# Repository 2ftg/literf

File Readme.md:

## What if hackRF, but cheap?

This repository contains hardware designs and software for the liteRF project,
a low cost, open source Software Defined Radio platform based on the popular HackRF design by Great Scott Gadgets.  

This is a living project and thus not suitable for manufacturing or any use. You have been warned.

We want to reduce the cost and availability problems with the parts chosen for the original HackRF.  
Our target is to at least halve the BOM cost and avoid as many of the unobtainium and obsolete parts.  
Especially those by Maxim.

This whole project started with me finding AT86RF215's on Digikey one night and discovering their IQ interface.   
It was re-invigorated by the [CaribouLite project](https://github.com/cariboulabs/cariboulite/blob/main/docs/smi/README.md) also named Lite and using the AT86RF215.

(photo by fd0 from https://github.com/fd0/hackrf-one-pictures)

This is the original hackRF, want to make it cheaper and to avoid problems with unobtainium parts.

Because all great artists steal, we will consider existing related projects when choosing parts.   
As that gives us access to existing, proven designs with support from the community.

### Component substitutions that have been decided on:
1. Maxim MAX2837+MAX5864 replaced by Microchip AT86RF215. Cheaper, more available.
2. Xilinx XC2C64A-7VQG100C CPLD replaced with Lattice ICE40LP1k-QN84
3. SiLabs/Skyworks Si5351C replaced by Hangzhou Ruimeng Tech MS5351M. Cheaper, AVAILABLE. Might require two or rethinking clocks.

Some links to candidate parts and information on them below.

#### Maxim MAX2837 Transceiver + MAX5864 AFE with AT86RF215
Both of these are expensive and hard to find. It might change now that Analog Devices owns Maxim, or get worse.   
Replacing these is the origin of this project. I had a terrible time sourcing them for my hackRF build.   

MAX2837 info:   
https://www.maximintegrated.com/en/products/comms/wireless-rf/MAX2837.html   
Datasheet: https://datasheets.maximintegrated.com/en/ds/MAX2837.pdf 

MAX5864 info:  
https://www.maximintegrated.com/en/products/analog/data-converters/analog-front-end-ics/MAX5864.html

MAX2837 covers 2300-2700MHz in turn AT86RF215 covers only a part of the same spectrum. The 2400-2400-2483.5MHz ISM band.
This is not a major problem as hacKRF uses a 2.4GHz IF with a SAW filter.   
This is compatible with using AT86RF215.

AT86RF215 info:
https://www.microchip.com/en-us/product/AT86RF215
Datasheet: https://ww1.microchip.com/downloads/en/DeviceDoc/45099A-AT86RF215_E_US_102714_Web.pdf

#### Xilinx XC2C64A-7VQG100C CPLD with Lattice ICE40LP1k-QN84 FPGA
0 stock and 52 week lead time on Digikey, nuff said:   
https://www.digikey.fi/en/products/detail/xilinx-inc/XC2C64A-7VQG100C/949460
Datasheet: https://docs.xilinx.com/v/u/en-US/ds311

In addition to sourcing problems, a 64 macrocell CPLD can't do what we want to the 128Mbit/second 64MHz DDR clocked LVDS interface AT86RF215 has.   
Thus we replace it with Lattice ICE40LP1k-QN84. This has a FOSS toolchain and a free tool chain from the manufacturer.   
It is used in the CaribouLite, so it works with AT86RF215 amd the gateware is under a permissive license. So we are not starting from 100% scratch.  
We need some fast programmable gluelogic here and Lattice iCE40 is a good choise due to low cost, good FOSS community and okay-ish [availability](https://octopart.com/ice40lp1k-qn84-lattice+semiconductor-22303412).   
I might have to reconsider this if I cannot source it or any iCE40 device with the same or larger amount of LUT's. I'm open to suggestions.   
iCE40LP family datasheet:    https://www.latticesemi.com/~/media/LatticeSemi/Documents/DataSheets/iCE/iCE40LPHXFamilyDataSheet.pdf

#### SiLabs/Skyworks Si5351C replaced with Hangzhou Ruimeng Tech MS5351M.

Skyworks Si5351C is in QFN case and has 8 outputs, compared to MS5351M's 3, so some work is likely needed. But they are register compatible and MS5351M 1:1 replaces Si5351B in almost all applications.   
This requires further thought in the clock tree side of things. 

Source and datasheet.   
https://lcsc.com/product-detail/Clock-Generators-Frequency-Synthesizers-PLL_Hangzhou-Ruimeng-Tech-MS5351M_C1509083.html   

QRP-Labs investigation that finds MS5351 meeting or exeeding Si5351.   
http://www.qrp-labs.com/synth/ms5351m.html

Si5351C stock situation:   
https://octopart.com/si5351c-b-gm-silicon+labs-24879781

### Component substitutions that are under consideration:
1. NXP LPC4320FBD144 MCU substitution with something cheaper and more available.
2. TI TPS62410 dual VREG with two Microchip switchers and point of load low noise LDO's for RF. Due to availability and noise.
3. Skyworks SKY13317 RF switch with Maxcend MXD8641. Due to price and availability. Also for better frontend.

Some links to candidate parts and information on them.

NXP LPC4320FBD144 has:   
ARM Cortex-M4F core capable of 204MHz and a Arm Cortex-M0 co-processor running at frequencies up to 204MHz.   
200kB SRAM
High-speed USB 2.0 Host/Device interface.

##### WCH CH32V307VCT6 MCU candidate.
I'm unsure if this is fast enough. It's RISC-V! 
Datasheet+SDK https://github.com/openwch/ch32v307   

LQFP100 case https://lcsc.com/product-detail/Microcontroller-Units-MCUs-MPUs-SOCs_WCH-Jiangsu-Qin-Heng-CH32V307VCT6_C2943979.html

Used in [iCEBreaker 1.99 hardware](https://github.com/icebreaker-fpga/icebreaker/tree/hw-v1.99-evaluation-designs/hardware/v1.99a) with Lattice iCE40UP5K.  

##### NXP i.MXRT MCU candidates

i.MX RT1024 Cortex-M7 @500 MHz 256 kB SRAM 144 LQFP 
i.MX RT1020 Cortex-M7 @500 MHz 256 kB SRAM 100 LQFP & 144 LQFP 

##### TPS62410DRCR info and repalcement candidates

[Octopart shows some stock, but only direct from TI or from Farnell, which is stingy about selling to individuals ](https://octopart.com/search?q=TPS62410DRCR&currency=EUR&specs=0)   
This is annoying and thus needs a good replacement. 

TPS62410 product page with info and datasheet:   
https://www.ti.com/product/TPS62410

##### Maxcend MXD8641 SP4T RF switch
Source and data.
https://lcsc.com/product-detail/RF-Switches_Maxscend-MXD8641_C285559.html

NanoVNA v2, they use Maxcend switches and later also MS5351M.   
https://github.com/nanovna-v2/NanoVNA2

Other Maxcend RF swithces are also available on LCSC.net (https://lcsc.com/products/RF-Switches_980.html?brand=11684)

#### Some parts selection logic I have used:   
Needs to be cheaper than what it's replacing.   
If not cheaper, then more available.   
If possible, already used and thus qualified by somebody else. Possibly lower risk of surprises that way.   
Higher performance than what it is replacing.   
Easier to use use than what it is replacing.      
If possible, the case should be easily soldered and inspected. So more QFN and TQFP, less BGA and LGA.   
Available from JLCPCB SMT assembly, LCSC.com , TME.eu, Mouser or Digikey.

##### Other minor motivations and changes:
PROPER REF DES on PCB.

One of these days I'll clean this up and use the wiki for all the component talk.

#### Contact
[@2ftg1](https://twitter.com/2ftg1/) on Twitter   
As ftg on Ircnet with shell, as ftg on Libera.Chat from time to time.

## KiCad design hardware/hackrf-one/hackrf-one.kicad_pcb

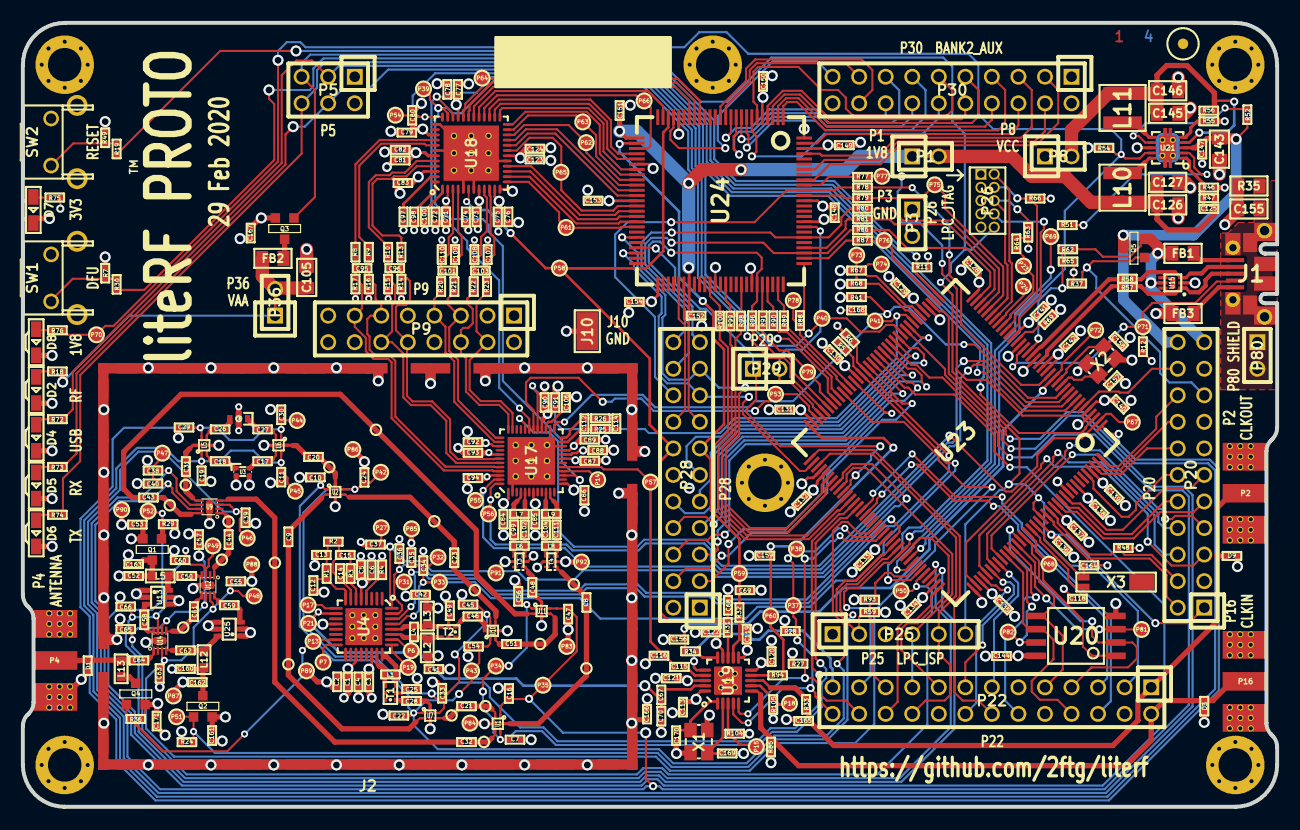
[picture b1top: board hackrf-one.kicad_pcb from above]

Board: 4 copper layers, 120.0 x 75.0 mm, 432 parts (0 on the bottom side), 316 nets.

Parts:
C1, C3, C5, C7, C10, C11, C16, C19, C22, C24, C29, C30, C33, C34, C35, C36, C37, C38, C39, C40, C45, C47, C54, C55, C56, C57, C60, C63, C65, C66, C67, C115, C125: 33pF; GSG-0402
C2, C4, C6, C87, C88, C89, C92, C93, C162, C163: 10nF; GSG-0402
C8, C21, C32, C43, C48, C51, C84, C85, C86, C94, C95, C96, C99, C101, C102, C103, C107, C108, C109, C110: 22pF; GSG-0402
C9, C17, C18, C20, C23, C25, C28, C31, C44, C46, C49, C50, C58, C59, C61, C62, C64, C71, C73, C75, C77, C79, C81, C83, C91, C113, C119, C120, C121, C122, C123, C128, C129, C130, C131, C132, C133, C134, C135, C136, C137, C138, C139, C140, C141, C142, C144, C147, C148, C149, C150, C151, C152, C153, C154, C166, C167: 100nF; GSG-0402
C12, C13: 330pF; GSG-0402
C14: 8p2; GSG-0402
C15, C112: 180pF; GSG-0402
C26, C27, C116, C156: 47pF; GSG-0402
C41, C42, C52, C68, C69, C70, C90, C159, C160, C165, C168: 100pF; GSG-0402
C53, C106, C161, C171: 1uF; GSG-0402
C72, C74, C76, C78, C80, C82, C124: 2.2uF; GSG-0402
C97, C98, C100: 330nF; GSG-0402
C104, C111: 3pF; GSG-0402
C105, C126, C127, C143, C145, C146: 10uF; GSG-0805
C114: 3.3nF; GSG-0402
C118, C157, C158, C164: 18pF; GSG-0402
C155: DNP; GSG-0805
C169, C170: DNP; GSG-0402
D1, D3, D9: GSG-DIODE-TVS-BI; GSG-0402
D2: VAALED; LTST-S220
D4: USBLED; LTST-S220
D5: RXLED; LTST-S220
D6: TXLED; LTST-S220
D7: VCCLED; LTST-S220
D8: 1V8LED; LTST-S220
FB1, FB2, FB3: FILTER; GSG-0805
J1: USB-MICRO-B; GSG-USB-MICROB-FCI-10103592-EXT
J2: RF-SHIELD-FRAME; GSG-SHIELD-BMI-S-230
J3: RF-SHIELD-COVER; GSG-NULL-MODULE
J4, J5, J6, J7, J8, J9: MOUNTING_HOLE; GSG-HOLE126MIL-COPPER
J10: GND_CLIP; GSG-TEST-POINT-S1751-46R
L1, L4, L6, L8, L9: DNP; GSG-0402
L2, L3, L5, L12, L13: 10uH; GSG-0603
L7: 6.2nH; GSG-0402
L10, L11: 4u7; GSG-NRG4026
MARK1MM: VAL**; GSG-MARK1MM
P1: 1V8; GSG-HEADER-1x2
P2: CLKOUT; GSG-SMA-73251-2120
P3: GND; GSG-HEADER-NOMARK-1x2
P4: ANTENNA; GSG-SMA-73251-2120
P5: LEDS; GSG-HEADER-2x3
P6: GPO4; GSG-TESTPOINT-50MIL
P7: GPO2; GSG-TESTPOINT-50MIL
P8: VCC; GSG-HEADER-1x2
P9: BASEBAND; GSG-HEADER-2x8
P13: GPO1; GSG-TESTPOINT-50MIL
P14: XCVR_CLKOUT; GSG-TESTPOINT-50MIL
P15: INTR; GSG-TESTPOINT-50MIL
P16: CLKIN; GSG-SMA-73251-2120
P17: GPO6; GSG-TESTPOINT-50MIL
P18: OEB; GSG-TESTPOINT-50MIL
P19: GPO3; GSG-TESTPOINT-50MIL
P20: GPIO; GSG-HEADER-2x11
P21: REF_IN; GSG-TESTPOINT-50MIL
P22: I2S; GSG-HEADER-2x13
P23: DBGEN; GSG-TESTPOINT-50MIL
P24: TRST; GSG-TESTPOINT-50MIL
P25: LPC_ISP; GSG-HEADER-1x6
P26: LPC_JTAG; GSG-50MIL-HEADER-2x5-TH
P27: MIXER_SDATA; GSG-TESTPOINT-50MIL
P28: SD; GSG-HEADER-2x11
P29: CPLD_JTAG; GSG-HEADER-1x2
P30: BANK2_AUX; GSG-HEADER-2x10
P31: MIXER_SCLK; GSG-TESTPOINT-50MIL
P32: MIXER_ENX; GSG-TESTPOINT-50MIL
P33: MIXER_RESETX; GSG-TESTPOINT-50MIL
P34: MIX_BYPASS; GSG-TESTPOINT-50MIL
P35: !MIX_BYPASS; GSG-TESTPOINT-50MIL
P36: VAA; GSG-HEADER-1x2
P37: SCL; GSG-TESTPOINT-50MIL
P38: SDA; GSG-TESTPOINT-50MIL
P39: SSP1_SCK; GSG-TESTPOINT-50MIL
P40: SSP1_MOSI; GSG-TESTPOINT-50MIL
P41: SSP1_MISO; GSG-TESTPOINT-50MIL
P42: TX; GSG-TESTPOINT-50MIL
P43: RX; GSG-TESTPOINT-50MIL
P44: HP; GSG-TESTPOINT-50MIL
P45: LP; GSG-TESTPOINT-50MIL
P46: TX_MIX_BP; GSG-TESTPOINT-50MIL
P47: RX_MIX_BP; GSG-TESTPOINT-50MIL
P48: TX_AMP; GSG-TESTPOINT-50MIL
P49: RX_AMP; GSG-TESTPOINT-50MIL
P50: AMP_BYPASS; GSG-TESTPOINT-50MIL
P51: !TX_AMP_PWR; GSG-TESTPOINT-50MIL
P52: !RX_AMP_PWR; GSG-TESTPOINT-50MIL
P53: CS_XCVR; GSG-TESTPOINT-50MIL
P54: CS_AD; GSG-TESTPOINT-50MIL
P55: TXENABLE; GSG-TESTPOINT-50MIL
P56: RXENABLE; GSG-TESTPOINT-50MIL
P57: XTAL2; GSG-TESTPOINT-50MIL
P58: GCK1; GSG-TESTPOINT-50MIL
P59: GCK2; GSG-TESTPOINT-50MIL
P60: SGPIO_CLK; GSG-TESTPOINT-50MIL
P61: DA0; GSG-TESTPOINT-50MIL
P62: DA7; GSG-TESTPOINT-50MIL
P63: DD0; GSG-TESTPOINT-50MIL
P64: DD9; GSG-TESTPOINT-50MIL
P65: DA4; GSG-TESTPOINT-50MIL
P66: DD5; GSG-TESTPOINT-50MIL
P67: RSSI; GSG-TESTPOINT-50MIL
P68: SPIFI_CS; GSG-TESTPOINT-50MIL
P69: VREGMODE; GSG-TESTPOINT-50MIL
P70: EN_1V8; GSG-TESTPOINT-50MIL
P71: ID; GSG-TESTPOINT-50MIL
P72, P75, P76, P77, P78, P79: GP_CLKIN; GSG-TESTPOINT-50MIL
P73: P1_2; GSG-TESTPOINT-50MIL
P74: P1_1; GSG-TESTPOINT-50MIL
P80: SHIELD; GSG-HEADER-NOMARK-1x2
P81: SPIFI_SIO2; GSG-TESTPOINT-50MIL
P82: SPIFI_SIO3; GSG-TESTPOINT-50MIL
P83, P84, P85, P86, P87, P88, P89, P90, P91, P92: GND; GSG-TESTPOINT-50MIL
Q1, Q2, Q3, Q4, Q5: MOSFET_P; SOT23GDS
R1, R2, R72, R75: 470; GSG-0402
R3: 22k; GSG-0402
R4: 51k; GSG-0402
R5, R6, R7, R11, R12, R24, R29, R36, R37, R41, R48, R49, R51, R52, R54, R59, R63, R64, R65, R66, R67, R68, R85, R93, R104, R105: 10k; GSG-0402
R8, R9, R10, R13, R73, R76: 1k; GSG-0402
R14, R15, R16, R17: 4k7; GSG-0402
R18, R27, R28, R74: 1k8; GSG-0402
R19, R30, R31, R32, R33, R34, R77, R78, R79, R80, R81, R86, R87, R88, R89, R90, R91, R94, R96, R98, R99, R100: 39; GSG-0402
R20, R21, R22, R23, R57, R58, R62: 0; GSG-0402
R25, R26: 475; GSG-0402
R35: DNP; GSG-0805
R46, R55: 162k; GSG-0402
R47: 330k; GSG-0402
R56: 715k; GSG-0402
R69: 12k; GSG-0402
SW1: DFU; GSG-SWITCH-FSMRA
SW2: RESET; GSG-SWITCH-FSMRA
T1: MIX_IN_BALUN; GSG-B0310J50100AHF
T2: MIX_OUT_BALUN; GSG-B0310J50100AHF
T3: RX_BALUN; GSG-2500BL14M100
T4: TX_BALUN; GSG-2500BL14M100
TESTPOINT-30MIL-MASKONLY, TESTPOINT-30MIL-MASKONLY#2, TESTPOINT-30MIL-MASKONLY#3, TESTPOINT-30MIL-MASKONLY#4, TESTPOINT-30MIL-MASKONLY#5, TESTPOINT-30MIL-MASKONLY#6, TESTPOINT-30MIL-MASKONLY#7, TESTPOINT-30MIL-MASKONLY#8, TESTPOINT-30MIL-MASKONLY#9, TESTPOINT-30MIL-MASKONLY#10, TESTPOINT-30MIL-MASKONLY#11, TESTPOINT-30MIL-MASKONLY#12, TESTPOINT-30MIL-MASKONLY#13, TESTPOINT-30MIL-MASKONLY#14, TESTPOINT-30MIL-MASKONLY#15, TESTPOINT-30MIL-MASKONLY#16, TESTPOINT-30MIL-MASKONLY#17: VAL**; GSG-TESTPOINT-30MIL-MASKONLY
U1, U2, U5, U6, U7, U10, U11: SKY13350; GSG-SKY13350-385LF
U3: RX_LOWPASS_FILTER; GSG-LP0603
U4: RFFC5072; GSG-QFN32
U8: RX_HIGHPASS_FILTER; GSG-HP-DEA
U9, U12, U14: SKY13317; GSG-SKY13317-373LF
U13, U25: MGA-81563; GSG-SOT363
U15: LXES1TBCC2-004; GSG-LXES1TBCC2-004
U17: MAX2837; GSG-QFN48-6
U18: MAX5864; GSG-QFN48-7
U19: SI5351C; GSG-QFN20-4
U20: W25Q80; GSG-SOIC8-208
U21: TPS62410; GSG-S-PVSON-N10
U23: LPC4320FBD144; GSG-LQFP144
U24: GSG-XC2C64A-7VQG100C; GSG-VQ100
X1: GSG-XTAL4PIN; GSG-XTAL3.2x2.5mm
X2: MCU_XTAL; GSG-XTAL3.2x2.5mm
X3: RTC_XTAL; GSG-XTAL-AB26TRQ

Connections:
!MIX_BYPASS: C16.1, C38.2, C47.2, P35.1, U1.1, U9.6, U11.5, U23.50
!RX_AMP_PWR: P52.1, Q1.G, R29.2, U23.106
!TX_AMP_PWR: P51.1, Q2.G, R24.1, U23.97
!VAA_ENABLE: P5.5, Q3.G, R11.2, U23.37
+1.8V: C151.1, C152.1, P1.1, U24.26, U24.57
/baseband/CLK0: R31.2, U19.13
/baseband/CLK1: R32.2, U19.12
/baseband/CLK2: R94.2, U19.9
/baseband/CLK3: R33.2, U19.8
/baseband/CLK5: C115.1, U19.17
/baseband/COM: C97.1, U18.47
/baseband/CPOUT+: C112.2, R25.1, U17.23
/baseband/CPOUT-: C112.1, R26.1, U17.24
/baseband/IA+: C101.1, C110.1, R20.1, U18.3
/baseband/IA-: C101.2, C109.1, R21.1, U18.4
/baseband/ID+: R13.1, U18.45
/baseband/ID-: R10.1, U18.44
/baseband/INTR: P15.1, R104.2, U19.3
/baseband/OEB: P18.1, R105.2, U19.7
/baseband/QA+: C103.2, C107.1, R23.1, U18.10
/baseband/QA-: C103.1, C108.1, R22.1, U18.9
/baseband/QD+: R8.1, U18.40
/baseband/QD-: R9.1, U18.41
/baseband/REFN: C98.1, U18.48
/baseband/REFP: C100.1, U18.1
/baseband/RXBBI+: P9.7, R20.2, U17.38
/baseband/RXBBI-: P9.5, R21.2, U17.37
/baseband/RXBBQ+: P9.6, R22.2, U17.36
/baseband/RXBBQ-: P9.4, R23.2, U17.35
/baseband/TXBBI+: C96.1, P9.12, R10.2, R15.1, U17.43
/baseband/TXBBI-: C96.2, P9.10, R13.2, R14.1, U17.42
/baseband/TXBBQ+: C95.2, P9.11, R9.2, R16.1, U17.44
/baseband/TXBBQ-: C95.1, P9.13, R8.2, R17.1, U17.45
/baseband/XA: C170.2, U19.1, X1.3
/baseband/XB: C169.2, U19.2, X1.1
/baseband/XCVR_CLKOUT: P14.1, U17.16
/baseband/XTAL2: C115.2, C116.1, P57.1, U17.17
/frontend/!ANT_BIAS: P13.1, Q4.G, R36.1, U4.15
/frontend/REF_IN: C67.2, C70.1, P21.1, U4.10
/frontend/RX_AMP_OUT: C50.2, U12.4
/frontend/TX_AMP_IN: C59.1, U12.8
/frontend/TX_AMP_OUT: C62.1, U14.4
/mcu/usb/power/ADC0_0: P20.20, U23.6
/mcu/usb/power/ADC0_2: P20.16, U23.143
/mcu/usb/power/ADC0_5: P20.18, U23.144
/mcu/usb/power/ADC0_6: P20.14, U23.142
/mcu/usb/power/B1AUX13: P28.16, U24.55
/mcu/usb/power/B1AUX14: P28.15, U24.56
/mcu/usb/power/B2AUX1: P30.18, U24.13
/mcu/usb/power/B2AUX2: P30.17, U24.12
/mcu/usb/power/B2AUX3: P30.16, U24.11
/mcu/usb/power/B2AUX4: P30.15, U24.10
/mcu/usb/power/B2AUX5: P30.14, U24.9
/mcu/usb/power/B2AUX6: P30.13, U24.8
/mcu/usb/power/B2AUX7: P30.12, U24.7
/mcu/usb/power/B2AUX8: P30.11, U24.6
/mcu/usb/power/B2AUX9: P30.10, U24.4
/mcu/usb/power/B2AUX10: P30.9, U24.3
/mcu/usb/power/B2AUX11: P30.8, U24.2
/mcu/usb/power/B2AUX12: P30.7, U24.1
/mcu/usb/power/B2AUX13: P30.6, U24.99
/mcu/usb/power/B2AUX14: P30.5, U24.97
/mcu/usb/power/B2AUX15: P30.4, U24.94
/mcu/usb/power/B2AUX16: P30.3, U24.92
/mcu/usb/power/BANK2F3M1: R77.2, U24.91
/mcu/usb/power/BANK2F3M2: P28.18, R78.2, U24.90
/mcu/usb/power/BANK2F3M3: R79.2, U24.89
/mcu/usb/power/BANK2F3M4: P28.22, R80.2, U24.81
/mcu/usb/power/BANK2F3M5: R81.2, U24.79
/mcu/usb/power/BANK2F3M6: P28.20, R86.2, U24.78
/mcu/usb/power/BANK2F3M7: R87.2, U24.77
/mcu/usb/power/BANK2F3M8: R88.2, U24.76
/mcu/usb/power/BANK2F3M9: R89.2, U24.74
/mcu/usb/power/BANK2F3M10: R90.2, U24.72
/mcu/usb/power/BANK2F3M11: R91.2, U24.71
/mcu/usb/power/BANK2F3M12: P28.21, R96.2, U24.70
/mcu/usb/power/BANK2F3M14: R98.2, U24.67
/mcu/usb/power/BANK2F3M15: R99.2, U24.64
/mcu/usb/power/BANK2F3M16: R100.2, U24.61
/mcu/usb/power/CPLD_TCK: P28.17, U23.74, U24.48
/mcu/usb/power/CPLD_TDI: P28.19, U23.78, U24.45
/mcu/usb/power/CPLD_TDO: P29.2, U23.69, U24.83
/mcu/usb/power/CPLD_TMS: P29.1, U23.82, U24.47
/mcu/usb/power/DBGEN: P23.1, R64.1, U23.28
/mcu/usb/power/DM: R58.1, U23.20
/mcu/usb/power/DP: R57.1, U23.18
/mcu/usb/power/EN1V8: P70.1, R54.2, R76.2, U21.9, U23.100
/mcu/usb/power/GCK0: P30.19, U24.22
/mcu/usb/power/GPIO3_8: P20.5, U23.110
/mcu/usb/power/GPIO3_9: P20.6, U23.113
/mcu/usb/power/GPIO3_10: P20.7, U23.115
/mcu/usb/power/GPIO3_11: P20.8, U23.117
/mcu/usb/power/GPIO3_12: P20.9, U23.132
/mcu/usb/power/GPIO3_13: P20.10, U23.133
/mcu/usb/power/GPIO3_14: P20.11, U23.134
/mcu/usb/power/GPIO3_15: P20.12, U23.140
/mcu/usb/power/GP_CLKIN: C156.1, P72.1, R34.1, U23.14
/mcu/usb/power/I2C1_SCL: P22.5, U23.88
/mcu/usb/power/I2C1_SDA: P22.6, U23.87
/mcu/usb/power/I2S0_RX_MCLK: P22.14, U23.73
/mcu/usb/power/I2S0_RX_SCK: P22.12, U23.120
/mcu/usb/power/I2S0_RX_SDA: P22.13, U23.116
/mcu/usb/power/I2S0_RX_WS: P22.15, U23.114
/mcu/usb/power/I2S0_TX_MCLK: P22.17, U23.99
/mcu/usb/power/I2S0_TX_SCK: P22.16, U23.112
/mcu/usb/power/ISP: P25.2, R59.2, U23.96
/mcu/usb/power/LED1: P5.3, R72.2, U23.3
/mcu/usb/power/LED2: P5.4, R73.2, U23.8
/mcu/usb/power/LED3: P5.6, R74.2, U23.103
/mcu/usb/power/P1_1: P74.1, R67.1, U23.42
/mcu/usb/power/P1_2: P73.1, R68.1, U23.43
/mcu/usb/power/P2_8: P22.23, R30.1, U23.98
/mcu/usb/power/P2_9: P22.21, R93.1, U23.102
/mcu/usb/power/P2_13: P22.22, U23.108
/mcu/usb/power/REG_OUT1: C145.2, C146.2, L11.1, P8.2, R56.1, U21.4
/mcu/usb/power/REG_OUT2: C125.1, C126.1, C127.1, L10.2, P1.2, R47.1
/mcu/usb/power/RESET: P22.3, P25.6, P26.10, R19.1, U23.128
/mcu/usb/power/RREF: R69.1, U23.24
/mcu/usb/power/RTCX1: C118.1, U23.125, X3.2
/mcu/usb/power/RTCX2: C164.1, U23.126, X3.1
/mcu/usb/power/RTC_ALARM: P20.2, U23.129
/mcu/usb/power/SD_CD: P28.3, U23.60
/mcu/usb/power/SD_CLK: P28.11, U23.45
/mcu/usb/power/SD_CMD: P28.9, U23.49
/mcu/usb/power/SD_DAT0: P28.7, U23.52
/mcu/usb/power/SD_DAT1: P28.6, U23.53
/mcu/usb/power/SD_DAT2: P28.5, U23.55
/mcu/usb/power/SD_DAT3: P28.4, U23.56
/mcu/usb/power/SD_POW: P28.10, U23.48
/mcu/usb/power/SD_VOLT0: P28.8, U23.51
/mcu/usb/power/SGPIO0: P75.1, R79.1, U23.32
/mcu/usb/power/SGPIO1: R81.1, U23.34
/mcu/usb/power/SGPIO2: R89.1, U23.62
/mcu/usb/power/SGPIO3: R90.1, U23.64
/mcu/usb/power/SGPIO4: R98.1, U23.79
/mcu/usb/power/SGPIO5: R99.1, U23.83
/mcu/usb/power/SGPIO6: R100.1, U23.84
/mcu/usb/power/SGPIO7: P76.1, R87.1, U23.38
/mcu/usb/power/SGPIO9: P77.1, R77.1, U23.7
/mcu/usb/power/SGPIO10: P78.1, R88.1, U23.61
/mcu/usb/power/SGPIO11: P79.1, R91.1, U23.66
/mcu/usb/power/SGPIO12: R96.1, U23.67
/mcu/usb/power/SGPIO13: R78.1, U23.15
/mcu/usb/power/SGPIO14: R80.1, U23.33
/mcu/usb/power/SGPIO15: R86.1, U23.35
/mcu/usb/power/SPIFI_CS: P68.1, U20.1, U23.124
/mcu/usb/power/SPIFI_MISO: P22.7, U20.2, U23.122
/mcu/usb/power/SPIFI_MOSI: P22.9, U20.5, U23.123
/mcu/usb/power/SPIFI_SCK: P22.8, U20.6, U23.118
/mcu/usb/power/SPIFI_SIO2: P81.1, U20.3, U23.121
/mcu/usb/power/SPIFI_SIO3: P82.1, U20.7, U23.119
/mcu/usb/power/TCK: P26.4, R66.2, U23.27
/mcu/usb/power/TDI: P26.8, U23.26
/mcu/usb/power/TDO: P26.6, R63.1, U23.31
/mcu/usb/power/TMS: P26.2, U23.30
/mcu/usb/power/U0_RXD: P22.19, P25.4, U23.81
/mcu/usb/power/U0_TXD: P22.20, P25.5, U23.75
/mcu/usb/power/USB_SHIELD: C155.1, J1.0, P80.1, P80.2, R35.1
/mcu/usb/power/VBAT: C136.1, P20.1, U23.127
/mcu/usb/power/VBUS: FB1.2, P20.21, Q5.S, R62.2, U15.5
/mcu/usb/power/VBUSCTRL: P20.17, Q5.G, R37.2
/mcu/usb/power/VIN: C143.1, C147.1, P20.22, Q5.D, R52.1, U21.3
/mcu/usb/power/VREGMODE: P69.1, R51.2, U23.101
/mcu/usb/power/WAKEUP: P20.4, R48.2, U23.130
/mcu/usb/power/XTAL1: C157.1, U23.12, X2.1
/mcu/usb/power/XTAL2: C158.1, U23.13, X2.3
AMP_BYPASS: C57.1, C65.2, P50.1, U12.6, U14.6, U23.104
CLK6: P22.25, U19.16
CLKIN: D3.2, P16.1, P22.2, R85.1, U19.6
CLKOUT: C165.1, D9.2, P2.1, P22.1, R33.1
CS_AD: P54.1, U18.36, U23.65
CS_XCVR: P53.1, U17.30, U23.70
DA0: P61.1, U18.13, U24.43
DA1: U18.14, U24.42
DA2: U18.15, U24.41
DA3: U18.16, U24.40
DA4: P65.1, U18.19, U24.39
DA5: U18.20, U24.37
DA6: U18.21, U24.36
DA7: P62.1, U18.22, U24.35
DD0: P63.1, U18.23, U24.34
DD1: U18.24, U24.33
DD2: U18.25, U24.32
DD3: U18.26, U24.30
DD4: U18.27, U24.29
DD5: P66.1, U18.28, U24.28
DD6: U18.29, U24.24
DD7: U18.30, U24.19
DD8: U18.31, U24.18
DD9: P64.1, U18.32, U24.17
GCK1: C68.1, P28.14, P58.1, R31.1, U18.6, U24.23
GCK2: C69.1, P28.13, P59.1, R32.1, U24.27
GND: C1.2, C2.2, C3.2, C4.2, C5.2, C6.2, C7.1, C10.1, C11.1, C12.2, C13.2, C16.2, C19.1, C22.1, C24.1, C25.2, C29.2, C30.2, C33.2, C34.2, C35.2, C36.2, C37.2, C38.1, C39.1, C40.1, C41.2, C42.2, C45.1, C47.1, C49.1, C52.2, C53.2, C54.2, C55.2, C56.2, C57.2, C60.1, C63.2, C65.1, C66.1, C68.2, C69.2, C70.2, C71.2, C72.2, C73.2, C74.2, C75.2, C76.2, C77.2, C78.2, C79.2, C80.2, C81.2, C82.2, C83.2, C84.2, C85.2, C86.2, C87.2, C88.2, C89.2, C90.2, C91.2, C92.2, C93.2, C94.2, C97.2, C98.2, C100.2, C105.2, C106.2, C107.2, C108.2, C109.2, C110.2, C113.2, C116.2, C118.2, C119.2, C120.2, C121.2, C122.2, C123.2, C124.2, C126.2, C127.2, C128.2, C129.2, C130.2, C131.2, C132.2, C133.2, C134.2, C135.2, C136.2, C137.2, C138.2, C139.2, C140.2, C141.2, C142.2, C143.2, C144.2, C145.1, C146.1, C147.2, C148.2, C149.2, C150.2, C151.2, C152.2, C153.2, C154.2, C155.2, C156.2, C157.2, C158.2, C159.2, C160.2, C161.2, C162.1, C163.1, C164.2, C165.2, C166.2, C167.2, C168.2, C169.1, C170.1, C171.2, D1.1, D2.1, D3.1, D4.1, D5.1, D6.1, D7.1, D8.1, D9.1, FB3.2, J2.0, J4.1, J5.1, J6.1, J7.1, J8.1, J9.1, J10.1, P2.2, P3.1, P3.2, P4.2, P5.1, P9.1, P9.2, P9.3, P9.8, P9.9, P9.14, P9.15, P9.16, P16.2, P20.13, P20.15, P20.19, P22.4, P22.10, P22.18, P25.1, P26.3, P26.5, P26.9, P28.2, P28.12, P30.2, P30.20, P83.1, P84.1, P85.1, P86.1, P87.1, P88.1, P89.1, P90.1, P91.1, P92.1, R4.1, R7.2, R14.2, R15.2, R16.2, R17.2, R35.2, R37.1, R41.1, R46.1, R54.1, R55.1, R65.1, R68.2, R69.2, R85.2, R93.2, SW1.0, SW2.0, SW2.1, T3.2, T3.5, T4.2, T4.5, U1.3, U2.3, U3.2, U3.3, U4.0, U4.12, U5.3, U6.3, U7.3, U8.2, U8.4, U9.0, U10.3, U11.3, U12.0, U13.1, U13.2, U13.4, U13.5, U14.0, U15.2, U17.0, U17.2, U17.22, U17.26, U18.0, U18.5, U18.7, U18.12, U18.17, U18.37, U18.42, U19.0, U20.4, U21.0, U21.8, U23.4, U23.19, U23.23, U23.40, U23.76, U23.109, U23.135, U24.21, U24.31, U24.62, U24.69, U24.84, U24.100, U25.1, U25.2, U25.4, U25.5, X1.2, X1.4, X2.2, X2.4
HP: C29.1, C30.1, P44.1, U5.5, U6.1, U23.1
LP: C11.2, C19.2, P45.1, U5.1, U6.5, U23.39
MCU_CLK: R34.2, U19.15
MIXER_ENX: C35.1, P32.1, R6.2, U4.30, U23.57
MIXER_RESETX: C34.1, P33.1, R5.2, U4.29, U23.58
MIXER_SCLK: C36.1, P31.1, U4.31, U23.95
MIXER_SDATA: C37.1, P27.1, U4.32, U23.80
MIX_BYPASS: C7.2, C56.1, P34.1, U1.5, U11.1, U23.86
MIX_CLK: C67.1, U19.19
unnamed: C8.2, U1.6
unnamed: C9.1, U7.2
unnamed: C9.2, U2.2
unnamed: C12.1, R1.2, U4.8
unnamed: C13.1, R1.1, R2.2
unnamed: C14.1, C15.1, R2.1, U4.7
unnamed: C14.2, R3.1, U4.6
unnamed: C15.2, R3.2
unnamed: C17.1, U3.4
unnamed: C17.2, U6.4
unnamed: C18.1, U5.2
unnamed: C18.2, U3.1
unnamed: C20.1, U6.6
unnamed: C20.2, U2.6
unnamed: C21.1, U1.2
unnamed: C21.2, U7.4
unnamed: C23.1, U10.4
unnamed: C23.2, U2.4
unnamed: C25.1, T1.2
unnamed: C26.1, U8.3
unnamed: C26.2, U5.4
unnamed: C27.1, U8.1
unnamed: C27.2, U6.2
unnamed: C28.1, T1.1
unnamed: C28.2, U7.6
unnamed: C31.1, U9.5
unnamed: C31.2, U5.6
unnamed: C32.1, U1.4
unnamed: C32.2, U9.4
unnamed: C43.1, U9.8
unnamed: C43.2, U11.2
unnamed: C44.1, U12.1
unnamed: C44.2, U9.1
unnamed: C46.1, U10.6
unnamed: C46.2, T2.1
unnamed: C48.1, U11.6
unnamed: C49.2, T2.2
unnamed: C50.1, L5.2, U13.6
unnamed: C51.1, U11.4
unnamed: C51.2, U10.2
unnamed: C58.1, U14.8
unnamed: C58.2, U13.3
unnamed: C59.2, U25.3
unnamed: C61.1, U14.5
unnamed: C61.2, U12.5
unnamed: C62.2, L12.2, U25.6
unnamed: C64.1, U14.1
unnamed: C64.2, D1.2, L13.2, P4.1
unnamed: C99.1, L7.1, U17.4
unnamed: C99.2, L6.1, T3.4
unnamed: C102.1, L7.2, U17.5
unnamed: C102.2, L6.2, T3.3
unnamed: C104.1, L9.1, U17.10
unnamed: C104.2, L8.1, T4.4
unnamed: C105.1, FB2.2, P36.2
unnamed: C106.1, U17.27
unnamed: C111.1, L9.2, U17.11
unnamed: C111.2, L8.2, T4.3
unnamed: C114.1, R26.2
unnamed: C114.2, R25.2
unnamed: C125.2, R46.2, R47.2, U21.1
unnamed: C160.1, C162.2, L12.1, Q2.D
unnamed: C52.1, C163.2, L5.1, Q1.D
unnamed: D2.2, R18.1
unnamed: D4.2, R72.1
unnamed: D5.2, R73.1
unnamed: D6.2, R74.1
unnamed: D7.2, R75.1
unnamed: D8.2, R76.1
unnamed: FB1.1, J1.1
unnamed: FB2.1, Q3.D
unnamed: FB3.1, J1.5
unnamed: J1.2, R58.2, U15.3
unnamed: J1.3, R57.2, U15.1
unnamed: J1.4, P71.1, R12.2, U23.22
unnamed: L1.1, T1.4, U4.23
unnamed: L1.2, T1.3, U4.24
unnamed: L2.1, L4.2, T2.4, U4.27
unnamed: L3.1, L4.1, T2.3, U4.28
unnamed: L10.1, U21.10
unnamed: L11.2, U21.6
unnamed: L13.1, Q4.D
unnamed: P6.1, U4.26
unnamed: P7.1, U4.16
unnamed: P17.1, U4.9
unnamed: P19.1, U4.25
unnamed: P24.1, U23.29
unnamed: R4.2, U4.4
unnamed: R19.2, R49.2, SW2.2
unnamed: R7.1, R30.2, SW1.2
unnamed: R51.1, U21.2
unnamed: R52.2, U21.7
unnamed: R55.2, R56.2, U21.5
unnamed: R62.1, R65.2, U23.21
RSSI: P67.1, U17.32, U23.2
RX: C10.2, C22.2, C54.1, P43.1, U2.1, U7.1, U10.1, U23.91
RXENABLE: P56.1, U17.48, U23.10
RX_AMP: C60.2, C66.2, P49.1, U12.3, U14.7, U23.105
RX_IF: C48.2, T3.1
RX_MIX_BP: C40.2, P47.1, U9.7, U23.54
SCL: P22.26, P37.1, R28.2, U19.4, U23.92
SDA: P22.24, P38.1, R27.2, U19.5, U23.93
SGPIO_CLK: C159.1, P60.1, R94.1, U23.72
SSP1_MISO: C168.1, P41.1, U17.29, U23.44
SSP1_MOSI: P40.1, U17.31, U18.34, U23.47
SSP1_SCK: P39.1, U17.15, U18.35, U23.68
TX: C24.2, C33.1, C45.2, P42.1, U2.5, U7.5, U10.5, U23.85
TXENABLE: P55.1, U17.47, U23.9
TX_AMP: C55.1, C63.1, P48.1, U12.7, U14.3, U23.63
TX_IF: C8.1, T4.1
TX_MIX_BP: C39.2, P46.1, U9.3, U23.46
VAA: C3.1, C4.1, C5.1, C6.1, C41.1, C42.1, C53.1, C71.1, C72.1, C73.1, C74.1, C75.1, C76.1, C77.1, C78.1, C79.1, C80.1, C81.1, C82.1, C83.1, C84.1, C85.1, C86.1, C87.1, C89.1, C90.1, C91.1, C92.1, C93.1, C94.1, C161.1, C166.1, C171.1, L2.2, L3.2, P36.1, Q1.S, Q2.S, Q4.S, R18.2, R24.2, R29.1, R36.2, U4.5, U4.22, U17.1, U17.7, U17.13, U17.19, U17.21, U17.28, U17.39, U17.41, U17.46, U18.2, U18.8, U18.11, U18.33, U18.39, U18.43, U18.46
VCC: C1.1, C2.1, C88.1, C113.1, C119.1, C120.1, C121.1, C122.1, C123.1, C124.1, C128.1, C129.1, C130.1, C131.1, C132.1, C133.1, C134.1, C135.1, C137.1, C138.1, C139.1, C140.1, C141.1, C142.1, C144.1, C148.1, C149.1, C150.1, C153.1, C154.1, C167.1, P5.2, P8.1, P20.3, P22.11, P26.1, P28.1, P30.1, Q3.S, R5.1, R6.1, R11.1, R12.1, R27.1, R28.1, R48.1, R49.1, R59.1, R63.2, R64.2, R66.1, R67.2, R75.2, R104.1, R105.1, SW1.1, U4.19, U17.20, U18.18, U19.10, U19.11, U19.14, U19.18, U19.20, U20.8, U23.5, U23.16, U23.17, U23.25, U23.36, U23.41, U23.59, U23.71, U23.77, U23.94, U23.107, U23.111, U23.131, U23.137, U23.141, U24.5, U24.38, U24.51, U24.88, U24.98
XCVR_EN: R41.2, U17.25, U23.11

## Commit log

2020-02-29 Added a few lines to README.MD about the project
2020-02-29 smol pcb silk tweak
2020-02-29 additional small silk tweak
2022-04-21 Brought readme.md more up to speed.
    Getting things closer to current reality and aims.
2022-04-21 Updated to current revision
    Updated to current revision of things, but really needs stuff migrated to a wiki and a short overview with links to more info.
